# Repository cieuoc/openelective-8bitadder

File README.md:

Assignment: 8 bit full adder

+ Create a directory with your name
+ Inside it, 2 directories called Circuit, Enclosure

+ Place Kicad files and libraries inside Circuit
+ FreeCAD file FCstd and exported STL files inside Enclosure

+ Git add .
+ Git commit 
+ Git push

+ Create PR

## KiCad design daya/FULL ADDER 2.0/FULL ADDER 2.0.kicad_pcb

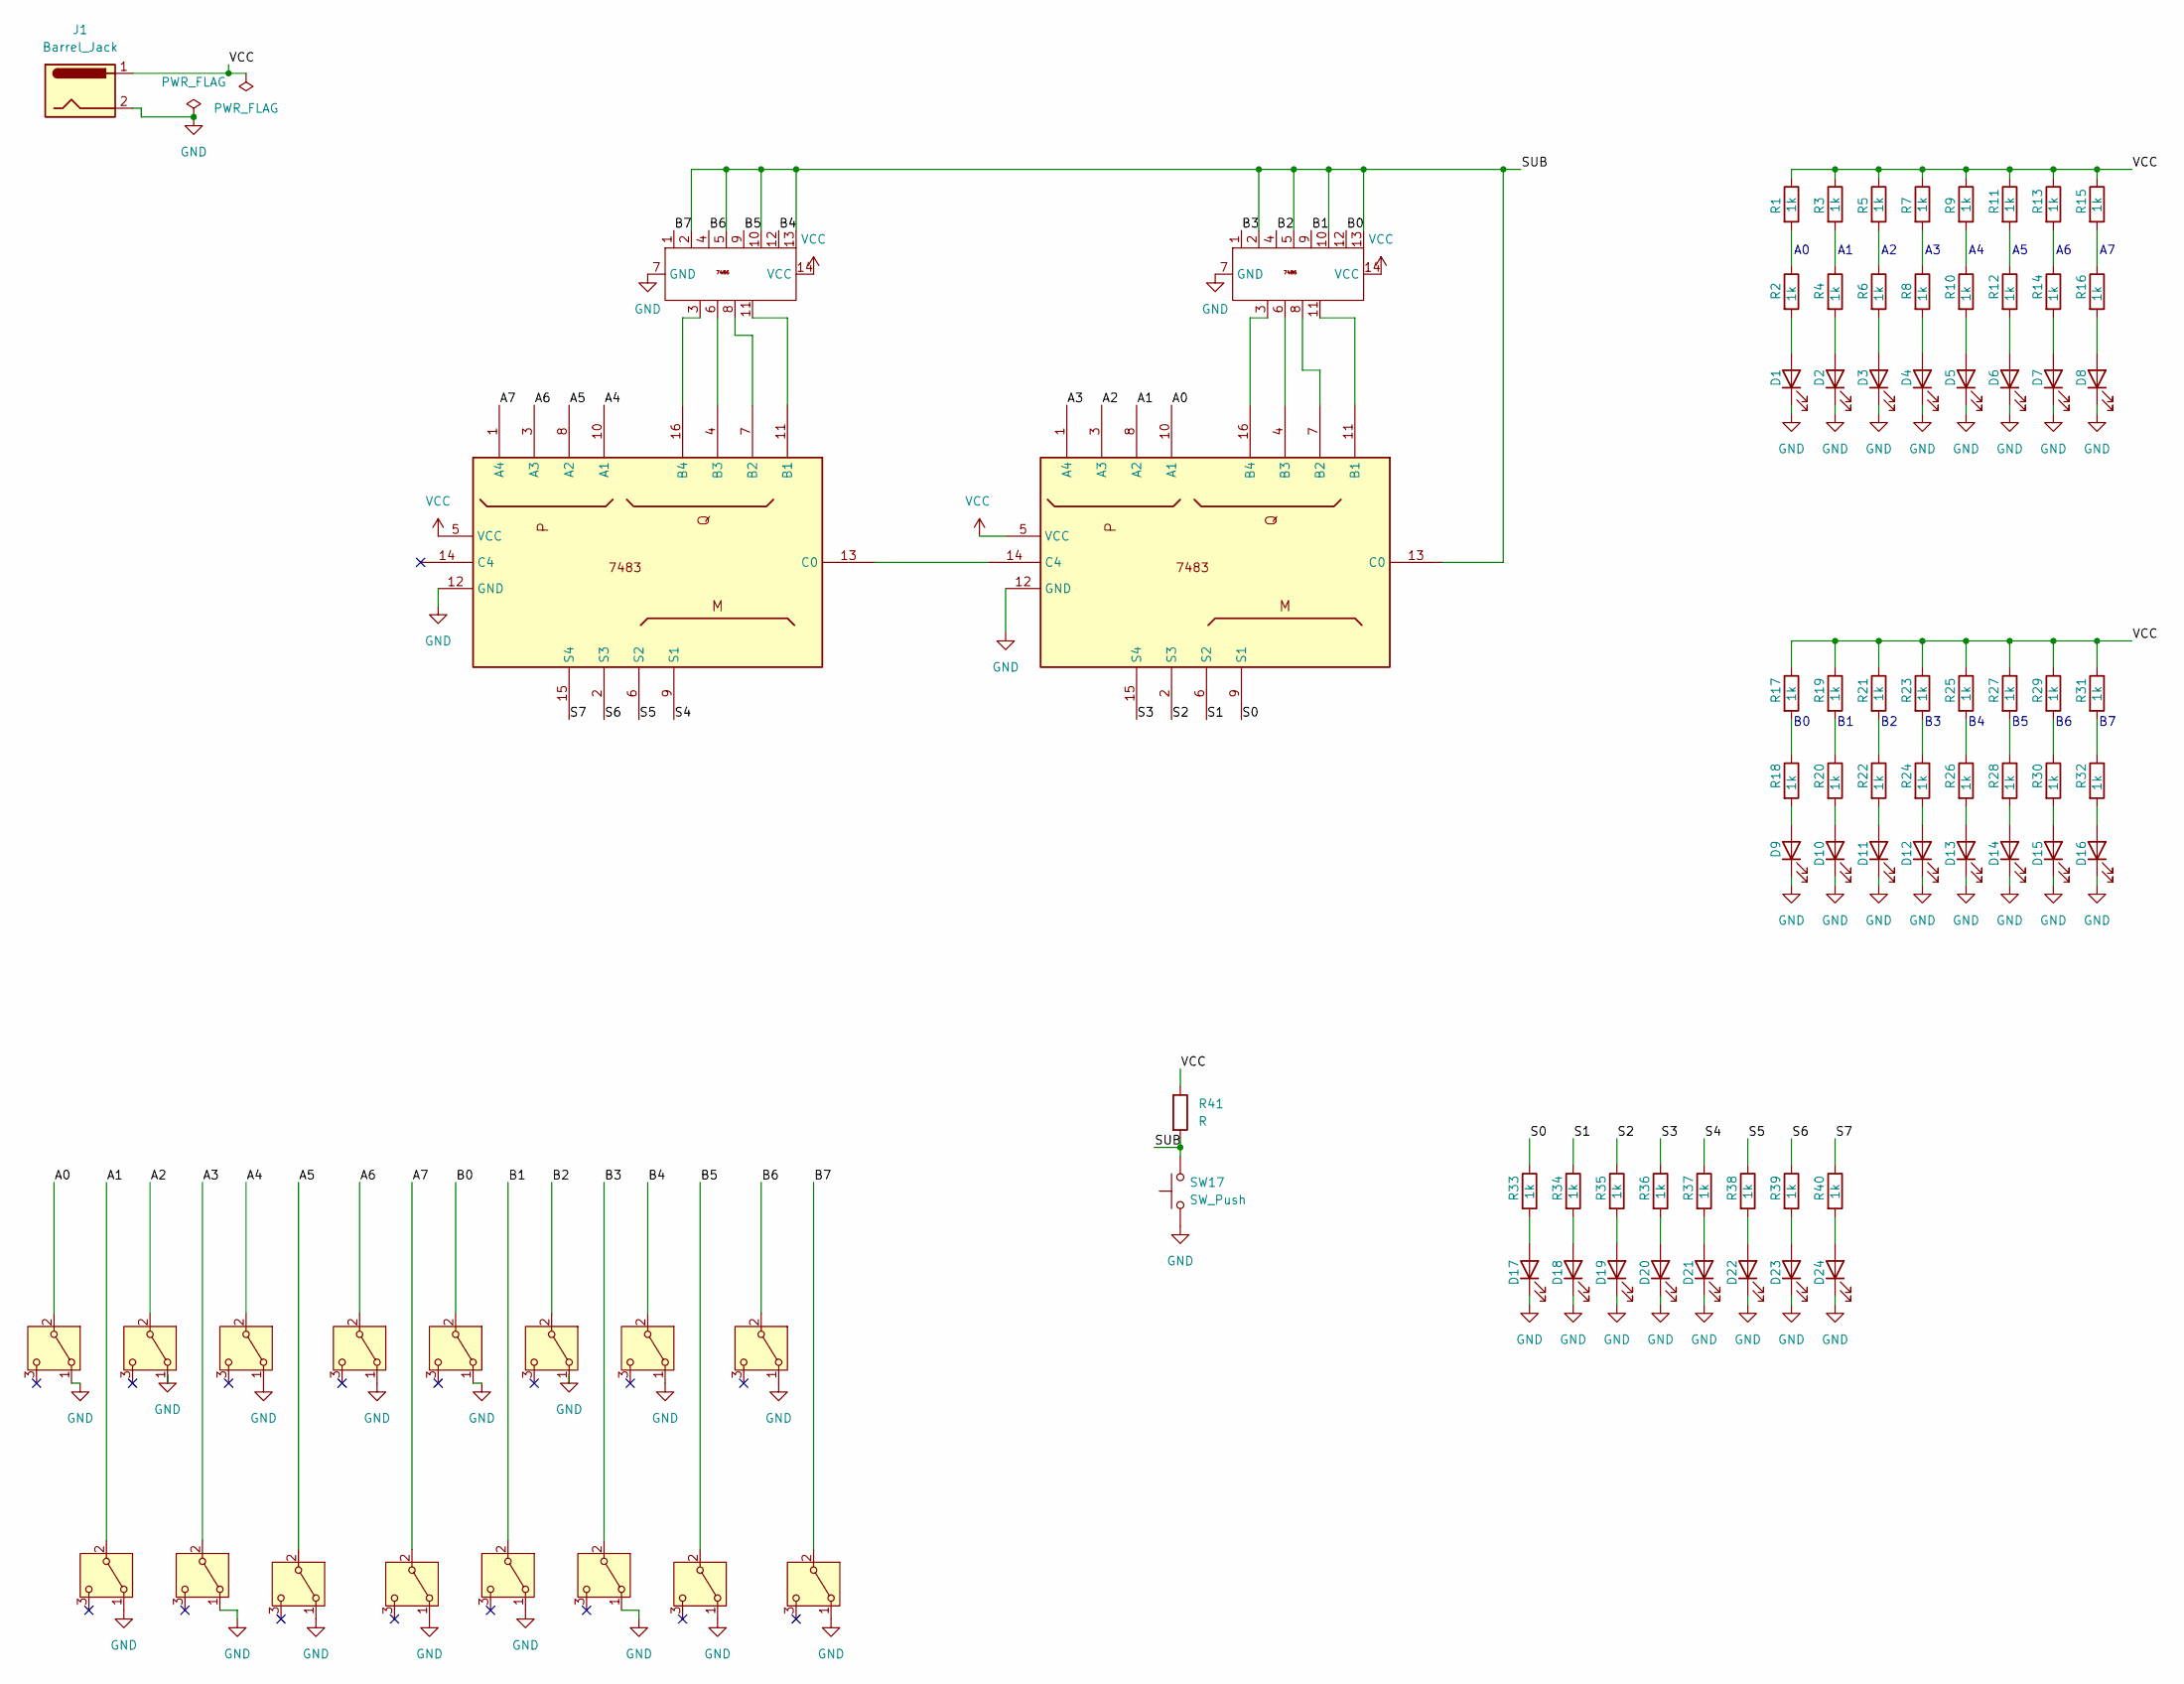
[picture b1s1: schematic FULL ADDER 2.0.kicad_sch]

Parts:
D1, D2, D3, D4, D5, D6, D7, D8, D9, D10, D11, D12, D13, D14, D15, D16, D17, D18, D19, D20, D21, D22, D23, D24: LED; LED_D3.0mm
J1: Barrel_Jack; BarrelJack_Horizontal
R1, R2, R3, R4, R5, R6, R7, R8, R9, R10, R11, R12, R13, R14, R15, R16, R17, R18, R19, R20, R21, R22, R23, R24, R25, R26, R27, R28, R29, R30, R31, R32, R33, R34, R35, R36, R37, R38, R39, R40: 1k; R_Axial_DIN0204_L3.6mm_D1.6mm_P5.08mm_Horizontal
R41: R; R_Axial_DIN0204_L3.6mm_D1.6mm_P5.08mm_Horizontal
SW1, SW2, SW3, SW4, SW5, SW6, SW7, SW8, SW9, SW10, SW11, SW12, SW13, SW14, SW15, SW16: SW_SPDT; adder switch
SW17: SW_Push; adder switch
U1, U4: DIP-16_W7.62mm
U2, U3: DIP-14_W7.62mm

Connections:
/A0: SW12.2 (B), U1.10 (A1)
/A1: SW9.2 (B), U1.8 (A2)
/A2: SW8.2 (B), U1.3 (A3)
/A3: SW6.2 (B), U1.1 (A4)
/A4: SW7.2 (B), U4.10 (A1)
/A5: SW3.2 (B), U4.8 (A2)
/A6: SW2.2 (B), U4.3 (A3)
/A7: SW4.2 (B), U4.1 (A4)
/B0: SW1.2 (B), U3.12
/B1: SW5.2 (B), U3.9
/B2: SW10.2 (B), U3.4
/B3: SW11.2 (B), U3.1
/B4: SW13.2 (B), U2.12
/B5: SW14.2 (B), U2.9
/B6: SW15.2 (B), U2.4
/B7: SW16.2 (B), U2.1
/S0: R33.1, U1.9 (S1)
/S1: R34.1, U1.6 (S2)
/S2: R35.1, U1.2 (S3)
/S3: R36.1, U1.15 (S4)
/S4: R37.1, U4.9 (S1)
/S5: R38.1, U4.6 (S2)
/S6: R39.1, U4.2 (S3)
/S7: R40.1, U4.15 (S4)
/SUB: R41.2, SW17.2, U1.13 (C0), U2.2, U2.5, U2.10, U2.13, U3.2, U3.5, U3.10, U3.13
GND: D1.1 (K), D2.1 (K), D3.1 (K), D4.1 (K), D5.1 (K), D6.1 (K), D7.1 (K), D8.1 (K), D9.1 (K), D10.1 (K), D11.1 (K), D12.1 (K), D13.1 (K), D14.1 (K), D15.1 (K), D16.1 (K), D17.1 (K), D18.1 (K), D19.1 (K), D20.1 (K), D21.1 (K), D22.1 (K), D23.1 (K), D24.1 (K), J1.2, SW1.1 (A), SW2.1 (A), SW3.1 (A), SW4.1 (A), SW5.1 (A), SW6.1 (A), SW7.1 (A), SW8.1 (A), SW9.1 (A), SW10.1 (A), SW11.1 (A), SW12.1 (A), SW13.1 (A), SW14.1 (A), SW15.1 (A), SW16.1 (A), SW17.1, U1.12 (GND), U2.7 (GND), U3.7 (GND), U4.12 (GND)
unnamed: D1.2 (A), R2.2
unnamed: D2.2 (A), R4.2
unnamed: D3.2 (A), R6.2
unnamed: D4.2 (A), R8.2
unnamed: D5.2 (A), R10.2
unnamed: D6.2 (A), R12.2
unnamed: D7.2 (A), R14.2
unnamed: D8.2 (A), R16.2
unnamed: D9.2 (A), R18.2
unnamed: D10.2 (A), R20.2
unnamed: D11.2 (A), R22.2
unnamed: D12.2 (A), R24.2
unnamed: D13.2 (A), R26.2
unnamed: D14.2 (A), R28.2
unnamed: D15.2 (A), R30.2
unnamed: D16.2 (A), R32.2
unnamed: D17.2 (A), R33.2
unnamed: D18.2 (A), R34.2
unnamed: D19.2 (A), R35.2
unnamed: D20.2 (A), R36.2
unnamed: D21.2 (A), R37.2
unnamed: D22.2 (A), R38.2
unnamed: D23.2 (A), R39.2
unnamed: D24.2 (A), R40.2
unnamed: R1.2, R2.1
unnamed: R3.2, R4.1
unnamed: R5.2, R6.1
unnamed: R7.2, R8.1
unnamed: R9.2, R10.1
unnamed: R11.2, R12.1
unnamed: R13.2, R14.1
unnamed: R15.2, R16.1
unnamed: R17.2, R18.1
unnamed: R19.2, R20.1
unnamed: R21.2, R22.1
unnamed: R23.2, R24.1
unnamed: R25.2, R26.1
unnamed: R27.2, R28.1
unnamed: R29.2, R30.1
unnamed: R31.2, R32.1
unnamed: U1.11 (B1), U3.11
unnamed: U1.7 (B2), U3.8
unnamed: U1.4 (B3), U3.6
unnamed: U1.16 (B4), U3.3
unnamed: U1.14 (C4), U4.13 (C0)
unnamed: U2.11, U4.11 (B1)
unnamed: U2.8, U4.7 (B2)
unnamed: U2.6, U4.4 (B3)
unnamed: U2.3, U4.16 (B4)
VCC: J1.1, R1.1, R3.1, R5.1, R7.1, R9.1, R11.1, R13.1, R15.1, R17.1, R19.1, R21.1, R23.1, R25.1, R27.1, R29.1, R31.1, R41.1, U1.5 (VCC), U2.14 (VCC), U3.14 (VCC), U4.5 (VCC)

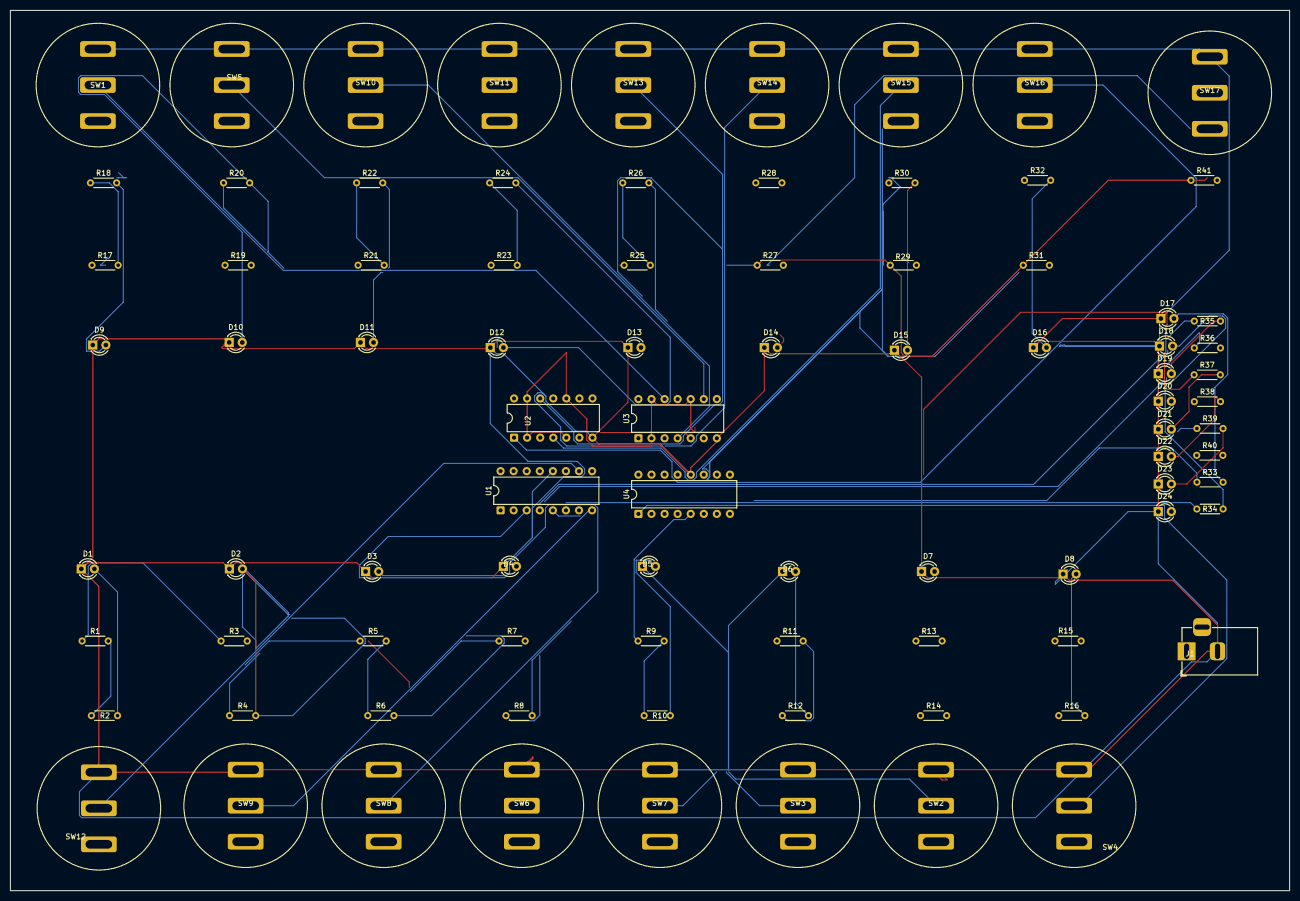
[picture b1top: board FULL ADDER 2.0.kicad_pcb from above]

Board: 2 copper layers, 248.5 x 171.0 mm, 87 parts (0 on the bottom side), 76 nets.

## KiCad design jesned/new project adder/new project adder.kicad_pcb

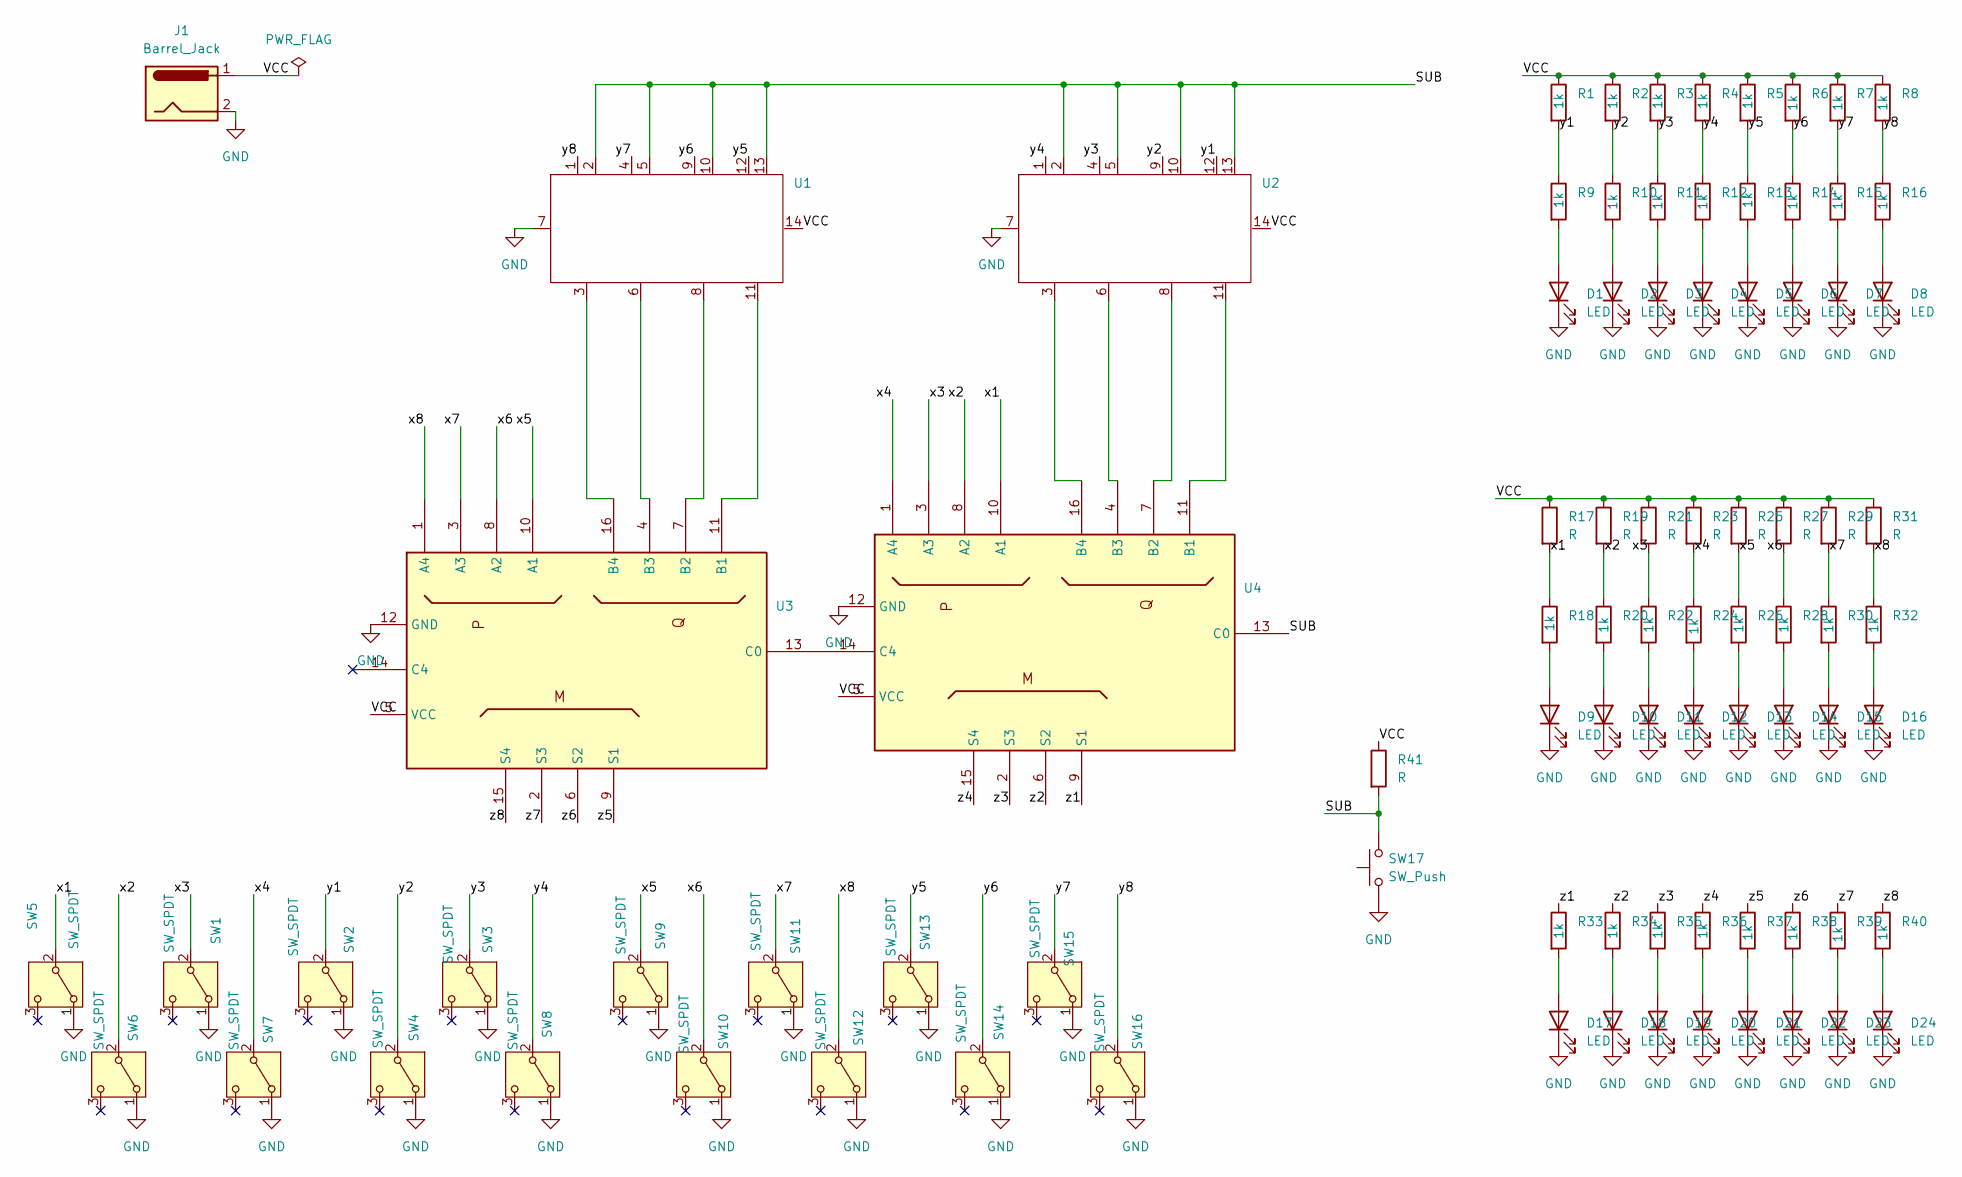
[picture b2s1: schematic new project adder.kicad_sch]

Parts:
D1, D2, D3, D4, D5, D6, D7, D8, D9, D10, D11, D12, D13, D14, D15, D16, D17, D18, D19, D20, D21, D22, D23, D24: LED; LED_D3.0mm
J1: Barrel_Jack; BarrelJack_Horizontal
R1, R2, R3, R4, R5, R6, R7, R8, R9, R10, R11, R12, R13, R14, R15, R16, R18, R20, R22, R24, R26, R28, R30, R32, R33, R34, R35, R36, R37, R38, R39, R40: 1k; R_Axial_DIN0204_L3.6mm_D1.6mm_P5.08mm_Horizontal
R17, R19, R21, R23, R25, R27, R29, R31, R41: R; R_Axial_DIN0204_L3.6mm_D1.6mm_P5.08mm_Horizontal
SW1, SW2, SW3, SW4, SW5, SW6, SW7, SW8, SW9, SW10, SW11, SW12, SW13, SW14, SW15, SW16: SW_SPDT; myswitch
SW17: SW_Push; myswitch
U1, U2: DIP-14_W7.62mm
U3, U4: DIP-16_W7.62mm

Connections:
/SUB: R41.2, SW17.2, U1.2, U1.5, U1.10, U1.13, U2.2, U2.5, U2.10, U2.13, U4.13 (C0)
/VCC: J1.1, R1.1, R2.1, R3.1, R4.1, R5.1, R6.1, R7.1, R8.1, R17.1, R19.1, R21.1, R23.1, R25.1, R27.1, R29.1, R31.1, R41.1, U1.14, U2.14, U3.5 (VCC), U4.5 (VCC)
/x1: R17.2, R18.1, SW5.2 (B), U4.10 (A1)
/x2: R19.2, R20.1, SW6.2 (B), U4.8 (A2)
/x3: R21.2, R22.1, SW1.2 (B), U4.3 (A3)
/x4: R23.2, R24.1, SW7.2 (B), U4.1 (A4)
/x5: R25.2, R26.1, SW9.2 (B), U3.10 (A1)
/x6: R27.2, R28.1, SW10.2 (B), U3.8 (A2)
/x7: R29.2, R30.1, SW11.2 (B), U3.3 (A3)
/x8: R31.2, R32.1, SW12.2 (B), U3.1 (A4)
/y1: R1.2, R9.1, SW2.2 (B), U2.12
/y2: R2.2, R10.1, SW4.2 (B), U2.9
/y3: R3.2, R11.1, SW3.2 (B), U2.4
/y4: R4.2, R12.1, SW8.2 (B), U2.1
/y5: R5.2, R13.1, SW13.2 (B), U1.12
/y6: R6.2, R14.1, SW14.2 (B), U1.9
/y7: R7.2, R15.1, SW15.2 (B), U1.4
/y8: R8.2, R16.1, SW16.2 (B), U1.1
/z1: R33.1, U4.9 (S1)
/z2: R34.1, U4.6 (S2)
/z3: R35.1, U4.2 (S3)
/z4: R36.1, U4.15 (S4)
/z5: R37.1, U3.9 (S1)
/z6: R38.1, U3.6 (S2)
/z7: R39.1, U3.2 (S3)
/z8: R40.1, U3.15 (S4)
GND: D1.1 (K), D2.1 (K), D3.1 (K), D4.1 (K), D5.1 (K), D6.1 (K), D7.1 (K), D8.1 (K), D9.1 (K), D10.1 (K), D11.1 (K), D12.1 (K), D13.1 (K), D14.1 (K), D15.1 (K), D16.1 (K), D17.1 (K), D18.1 (K), D19.1 (K), D20.1 (K), D21.1 (K), D22.1 (K), D23.1 (K), D24.1 (K), J1.2, SW1.1 (A), SW2.1 (A), SW3.1 (A), SW4.1 (A), SW5.1 (A), SW6.1 (A), SW7.1 (A), SW8.1 (A), SW9.1 (A), SW10.1 (A), SW11.1 (A), SW12.1 (A), SW13.1 (A), SW14.1 (A), SW15.1 (A), SW16.1 (A), SW17.1, U1.7, U2.7, U3.12 (GND), U4.12 (GND)
unnamed: D1.2 (A), R9.2
unnamed: D2.2 (A), R10.2
unnamed: D3.2 (A), R11.2
unnamed: D4.2 (A), R12.2
unnamed: D5.2 (A), R13.2
unnamed: D6.2 (A), R14.2
unnamed: D7.2 (A), R15.2
unnamed: D8.2 (A), R16.2
unnamed: D9.2 (A), R18.2
unnamed: D10.2 (A), R20.2
unnamed: D11.2 (A), R22.2
unnamed: D12.2 (A), R24.2
unnamed: D13.2 (A), R26.2
unnamed: D14.2 (A), R28.2
unnamed: D15.2 (A), R30.2
unnamed: D16.2 (A), R32.2
unnamed: D17.2 (A), R33.2
unnamed: D18.2 (A), R34.2
unnamed: D19.2 (A), R35.2
unnamed: D20.2 (A), R36.2
unnamed: D21.2 (A), R37.2
unnamed: D22.2 (A), R38.2
unnamed: D23.2 (A), R39.2
unnamed: D24.2 (A), R40.2
unnamed: U1.11, U3.11 (B1)
unnamed: U1.8, U3.7 (B2)
unnamed: U1.6, U3.4 (B3)
unnamed: U1.3, U3.16 (B4)
unnamed: U3.13 (C0), U4.14 (C4)
unnamed: U2.11, U4.11 (B1)
unnamed: U2.8, U4.7 (B2)
unnamed: U2.6, U4.4 (B3)
unnamed: U2.3, U4.16 (B4)

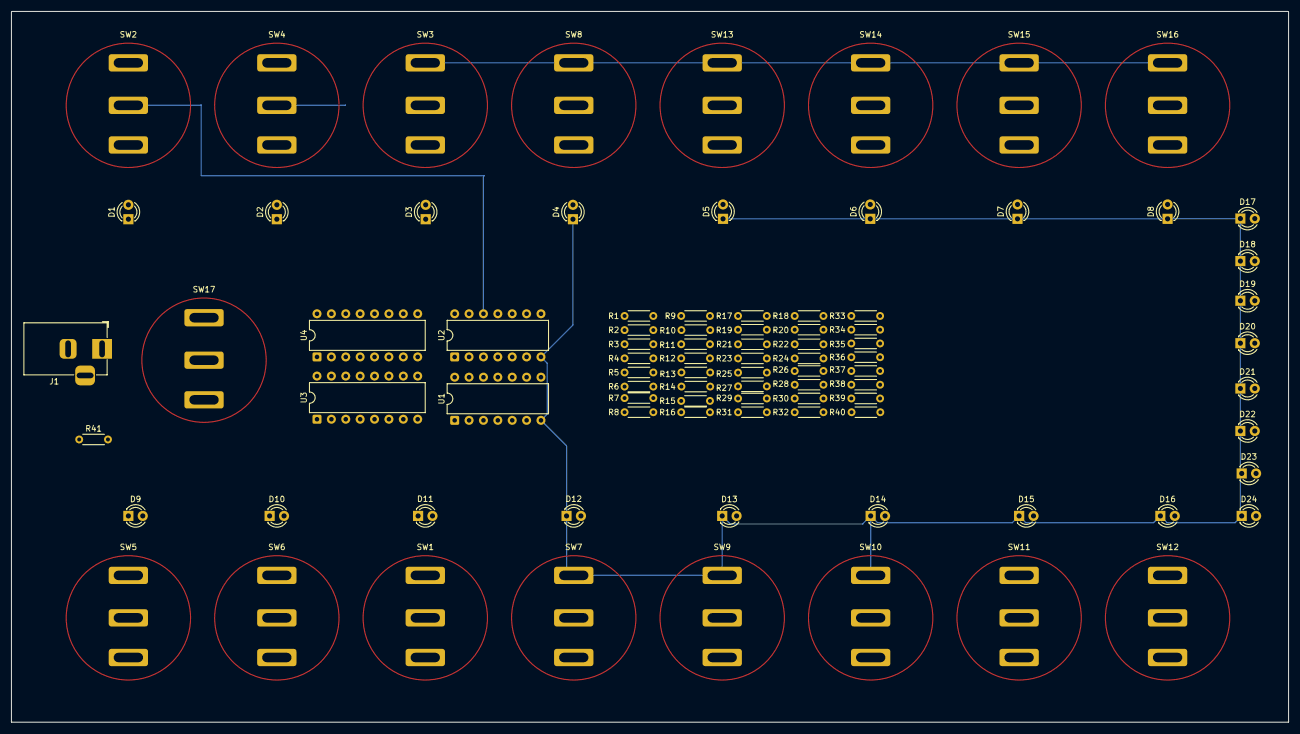
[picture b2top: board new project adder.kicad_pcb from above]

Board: 2 copper layers, 225.5 x 125.5 mm, 87 parts (0 on the bottom side), 60 nets.

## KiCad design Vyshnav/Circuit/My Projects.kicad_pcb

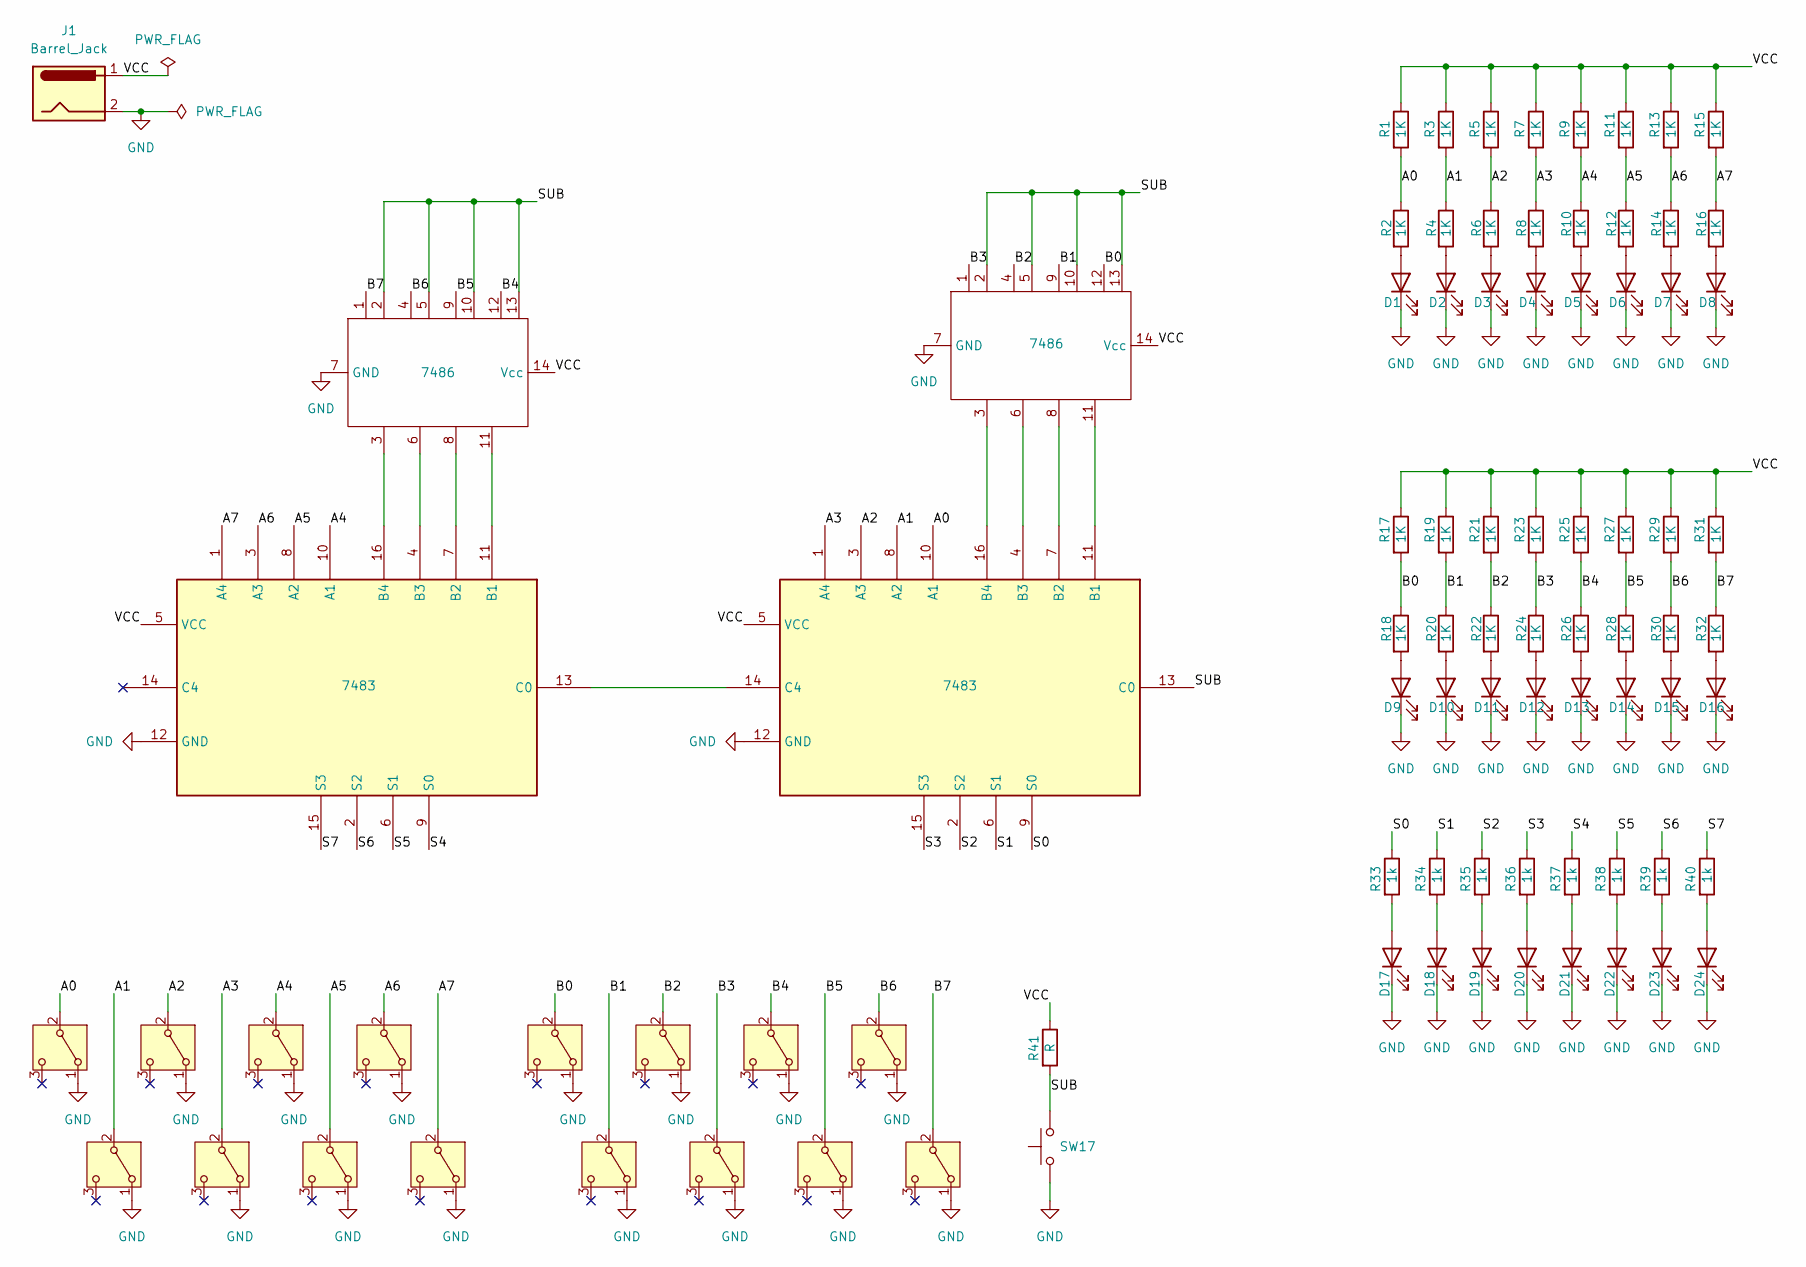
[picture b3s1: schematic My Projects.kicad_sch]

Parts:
D1, D2, D3, D4, D5, D6, D7, D8, D9, D10, D11, D12, D13, D14, D15, D16, D17, D18, D19, D20, D21, D22, D23, D24: LED; LED_D3.0mm
IC1, IC2: 7483; SMDIP-16_W7.62mm
IC3, IC4: 7486; DIP-14_W7.62mm
J1: Barrel_Jack; BarrelJack_Horizontal
R1, R2, R3, R4, R5, R6, R7, R8, R9, R10, R11, R12, R13, R14, R15, R16, R17, R18, R19, R20, R21, R22, R23, R24, R25, R26, R27, R28, R29, R30, R31, R32: 1K; R_Axial_DIN0204_L3.6mm_D1.6mm_P5.08mm_Horizontal
R33, R34, R35, R36, R37, R38, R39, R40: 1k; R_Axial_DIN0204_L3.6mm_D1.6mm_P5.08mm_Horizontal
R41: R; R_Axial_DIN0204_L3.6mm_D1.6mm_P5.08mm_Horizontal
SW1, SW2, SW3, SW4, SW5, SW6, SW7, SW8, SW9, SW10, SW11, SW12, SW13, SW14, SW15, SW16: SW_SPDT; SWITCH
SW17: SW_Push; SW_PUSH_6mm

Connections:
/A0: IC2.10 (A1), R1.2, R2.1, SW1.2 (B)
/A1: IC2.8 (A2), R3.2, R4.1, SW5.2 (B)
/A2: IC2.3 (A3), R5.2, R6.1, SW2.2 (B)
/A3: IC2.1 (A4), R7.2, R8.1, SW3.2 (B)
/A4: IC1.10 (A1), R9.2, R10.1, SW4.2 (B)
/A5: IC1.8 (A2), R11.2, R12.1, SW6.2 (B)
/A6: IC1.3 (A3), R13.2, R14.1, SW7.2 (B)
/A7: IC1.1 (A4), R15.2, R16.1, SW8.2 (B)
/B0: IC4.12, R17.2, R18.1, SW9.2 (B)
/B1: IC4.9, R19.2, R20.1, SW10.2 (B)
/B2: IC4.4, R21.2, R22.1, SW11.2 (B)
/B3: IC4.1, R23.2, R24.1, SW12.2 (B)
/B4: IC3.12, R25.2, R26.1, SW13.2 (B)
/B5: IC3.9, R27.2, R28.1, SW14.2 (B)
/B6: IC3.4, R29.2, R30.1, SW15.2 (B)
/B7: IC3.1, R31.2, R32.1, SW16.2 (B)
/S0: IC2.9 (S0), R33.1
/S1: IC2.6 (S1), R34.1
/S2: IC2.2 (S2), R35.1
/S3: IC2.15 (S3), R36.1
/S4: IC1.9 (S0), R37.1
/S5: IC1.6 (S1), R38.1
/S6: IC1.2 (S2), R39.1
/S7: IC1.15 (S3), R40.1
/SUB: IC2.13 (C0), IC3.2, IC3.5, IC3.10, IC3.13, IC4.2, IC4.5, IC4.10, IC4.13, R41.2, SW17.2
/VCC: IC1.5 (VCC), IC2.5 (VCC), IC3.14 (Vcc), IC4.14 (Vcc), J1.1, R1.1, R3.1, R5.1, R7.1, R9.1, R11.1, R13.1, R15.1, R17.1, R19.1, R21.1, R23.1, R25.1, R27.1, R29.1, R31.1, R41.1
GND: D1.1 (K), D2.1 (K), D3.1 (K), D4.1 (K), D5.1 (K), D6.1 (K), D7.1 (K), D8.1 (K), D9.1 (K), D10.1 (K), D11.1 (K), D12.1 (K), D13.1 (K), D14.1 (K), D15.1 (K), D16.1 (K), D17.1 (K), D18.1 (K), D19.1 (K), D20.1 (K), D21.1 (K), D22.1 (K), D23.1 (K), D24.1 (K), IC1.12 (GND), IC2.12 (GND), IC3.7 (GND), IC4.7 (GND), J1.2, SW1.1 (A), SW2.1 (A), SW3.1 (A), SW4.1 (A), SW5.1 (A), SW6.1 (A), SW7.1 (A), SW8.1 (A), SW9.1 (A), SW10.1 (A), SW11.1 (A), SW12.1 (A), SW13.1 (A), SW14.1 (A), SW15.1 (A), SW16.1 (A), SW17.1
unnamed: D1.2 (A), R2.2
unnamed: D2.2 (A), R4.2
unnamed: D3.2 (A), R6.2
unnamed: D4.2 (A), R8.2
unnamed: D5.2 (A), R10.2
unnamed: D6.2 (A), R12.2
unnamed: D7.2 (A), R14.2
unnamed: D8.2 (A), R16.2
unnamed: D9.2 (A), R18.2
unnamed: D10.2 (A), R20.2
unnamed: D11.2 (A), R22.2
unnamed: D12.2 (A), R24.2
unnamed: D13.2 (A), R26.2
unnamed: D14.2 (A), R28.2
unnamed: D15.2 (A), R30.2
unnamed: D16.2 (A), R32.2
unnamed: D17.2 (A), R33.2
unnamed: D18.2 (A), R34.2
unnamed: D19.2 (A), R35.2
unnamed: D20.2 (A), R36.2
unnamed: D21.2 (A), R37.2
unnamed: D22.2 (A), R38.2
unnamed: D23.2 (A), R39.2
unnamed: D24.2 (A), R40.2
unnamed: IC1.11 (B1), IC3.11
unnamed: IC1.7 (B2), IC3.8
unnamed: IC1.4 (B3), IC3.6
unnamed: IC1.16 (B4), IC3.3
unnamed: IC1.13 (C0), IC2.14 (C4)
unnamed: IC2.11 (B1), IC4.11
unnamed: IC2.7 (B2), IC4.8
unnamed: IC2.4 (B3), IC4.6
unnamed: IC2.16 (B4), IC4.3

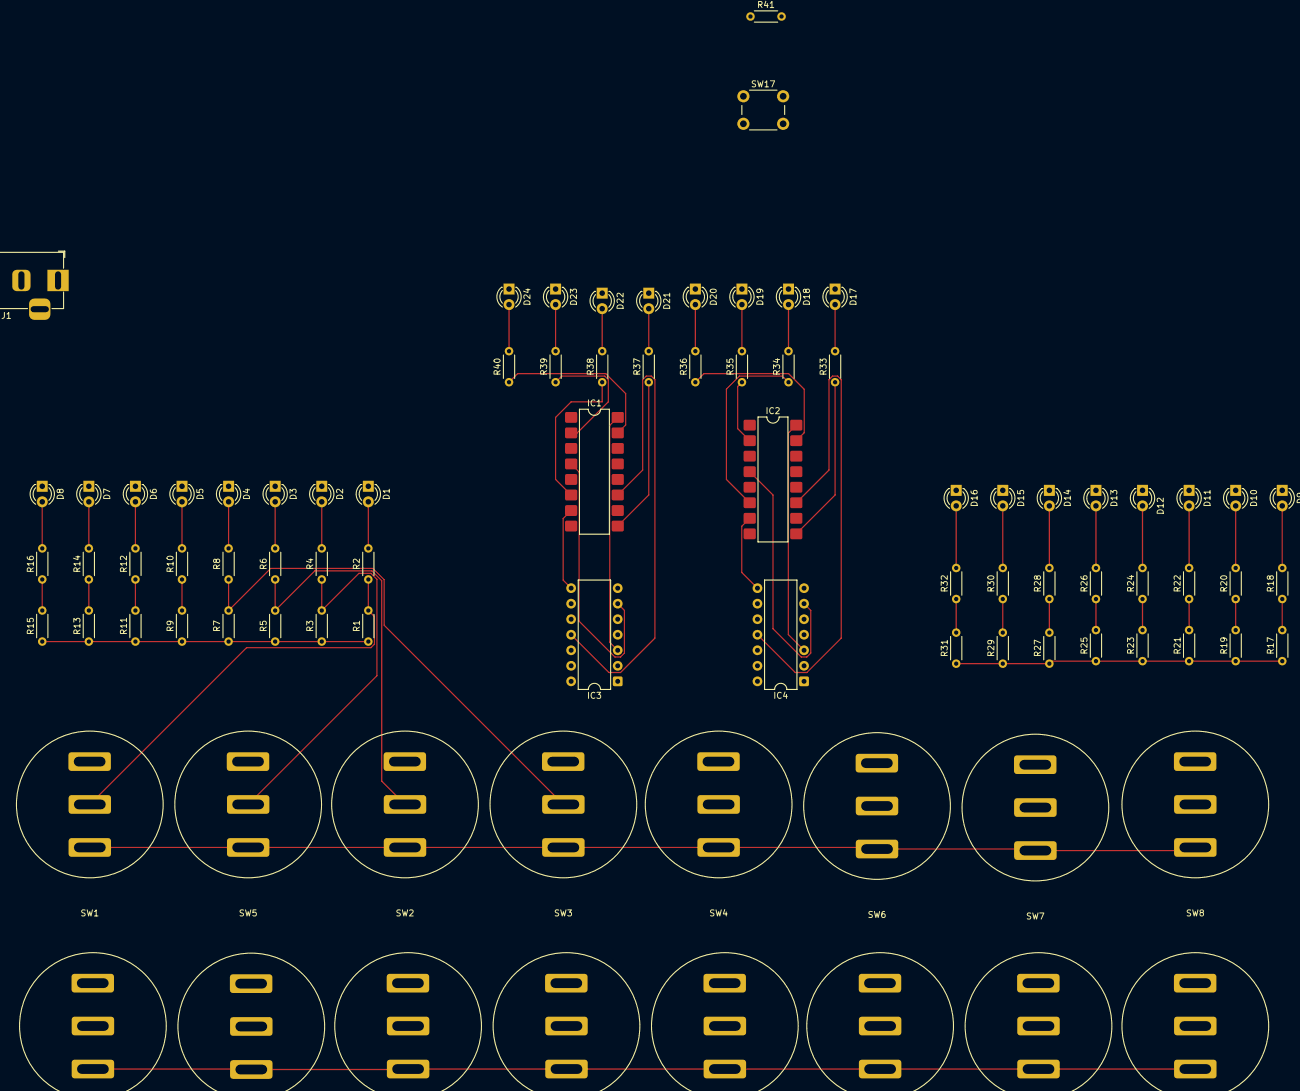
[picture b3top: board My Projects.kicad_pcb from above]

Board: 2 copper layers, 87 parts (0 on the bottom side), 60 nets.

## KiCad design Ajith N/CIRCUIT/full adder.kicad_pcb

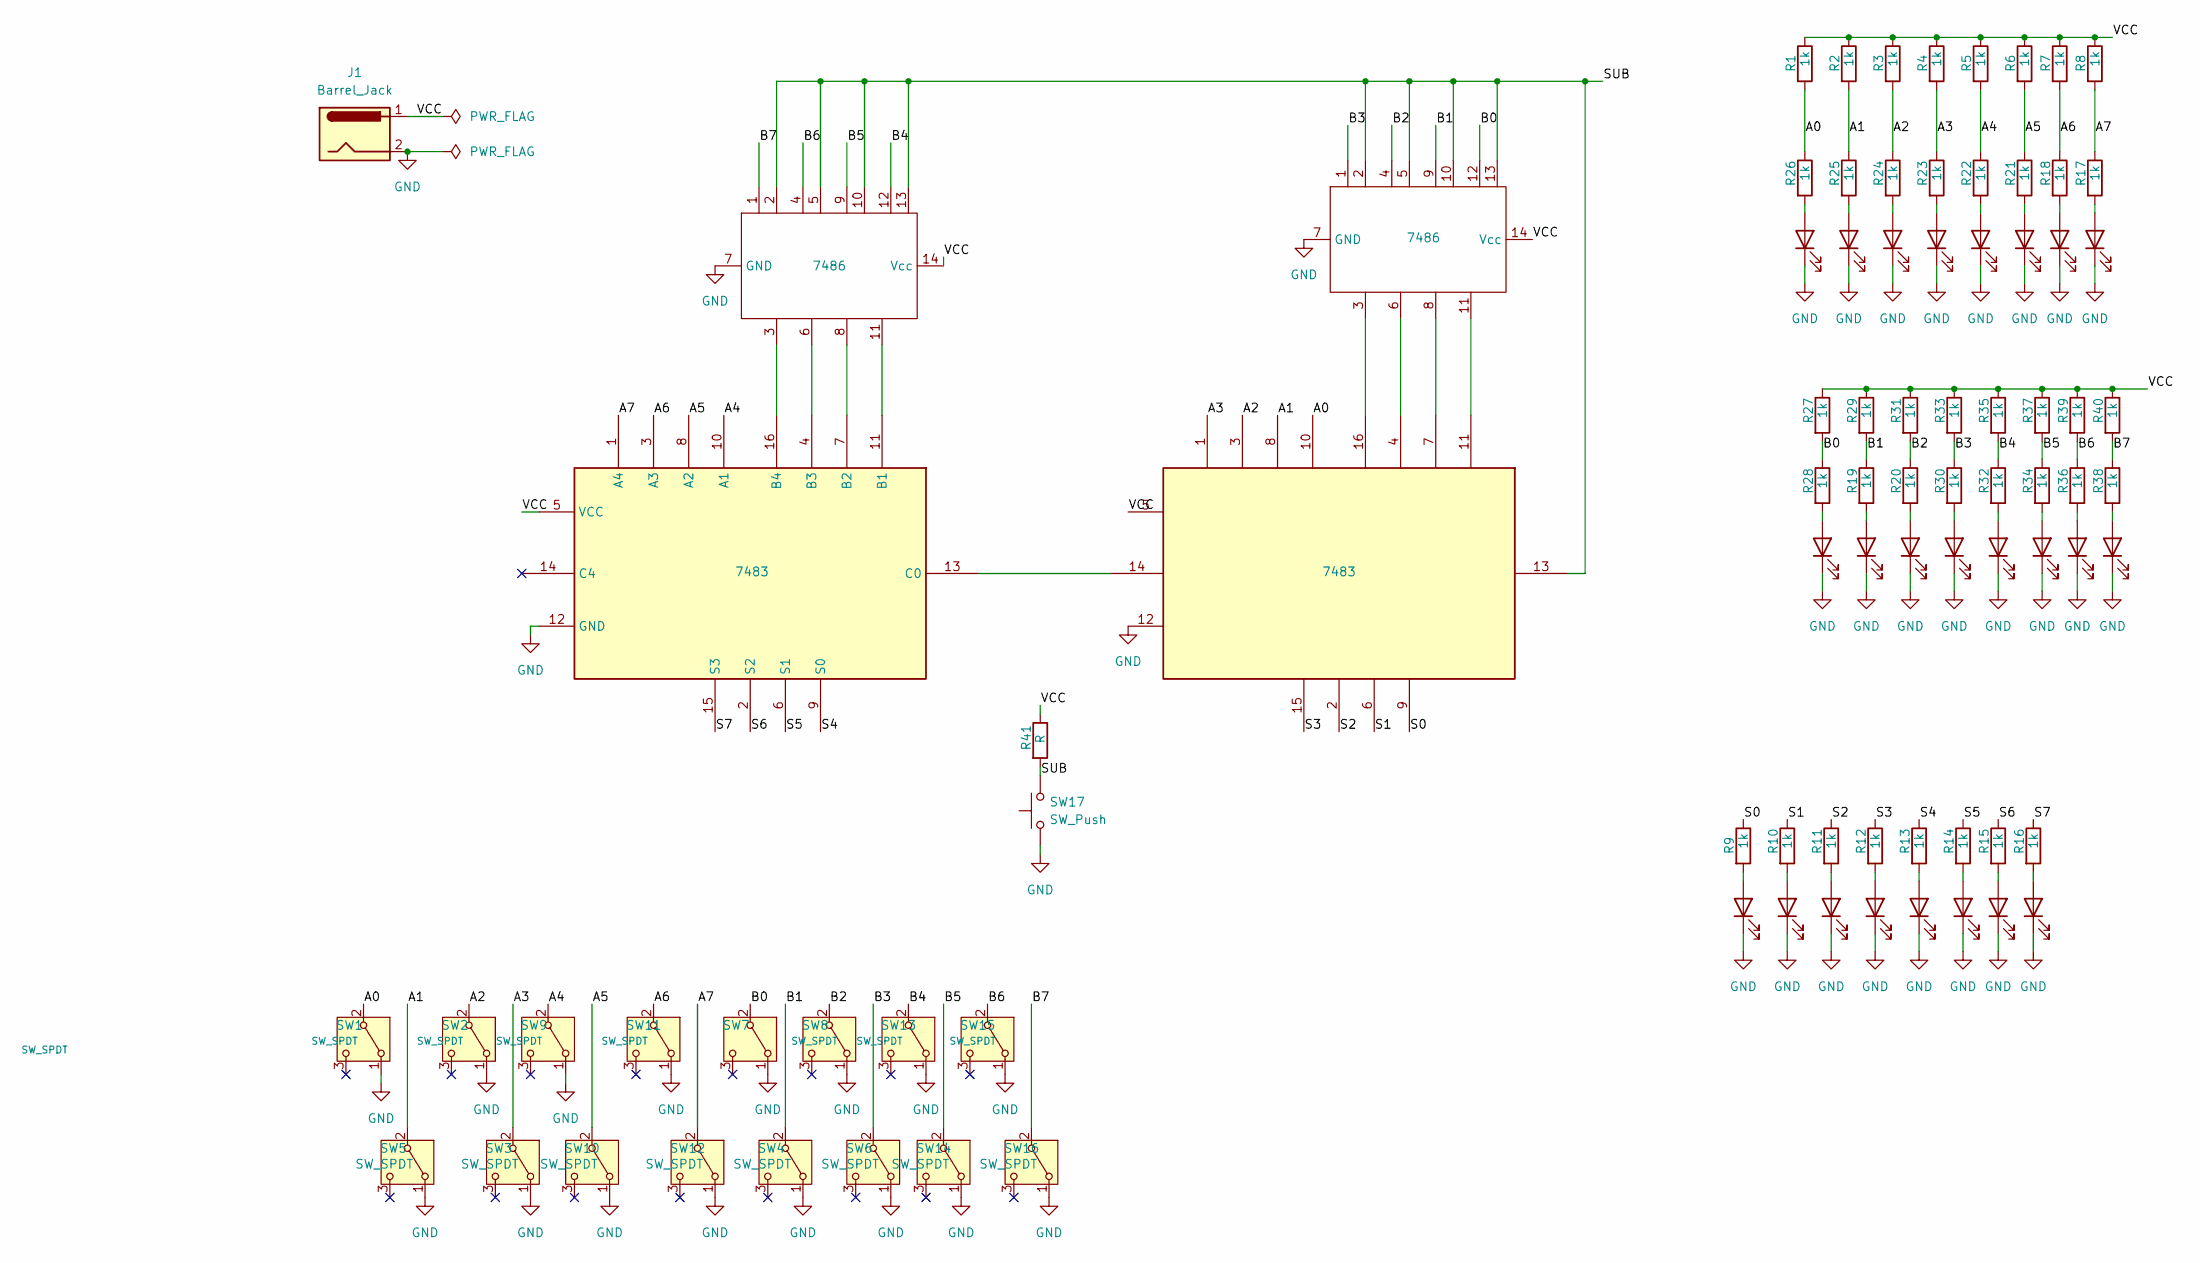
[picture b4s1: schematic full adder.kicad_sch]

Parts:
D1, D2, D3, D4, D5, D6, D7, D8, D9, D10, D11, D12, D13, D14, D15, D16, D18, D19, D20, D21, D22, D23, D24, D25: LED; LED_D3.0mm
IC1, IC2: 7483; DIP-16_W7.62mm
IC3, IC4: 7486; DIP-14_W7.62mm
J1: Barrel_Jack; BarrelJack_GCT_DCJ200-10-A_Horizontal
R1, R2, R3, R4, R5, R6, R7, R8, R9, R10, R11, R12, R13, R14, R15, R16, R17, R18, R19, R20, R21, R22, R23, R24, R25, R26, R27, R28, R29, R30, R31, R32, R33, R34, R35, R36, R37, R38, R39, R40: 1k; R_Axial_DIN0204_L3.6mm_D1.6mm_P5.08mm_Horizontal
R41: R; R_Axial_DIN0204_L3.6mm_D1.6mm_P5.08mm_Horizontal
SW1, SW2, SW3, SW4, SW5, SW6, SW7, SW8, SW9, SW10, SW11, SW12, SW13, SW14, SW15, SW16: SW_SPDT; LED SWITCH3pin
SW17: SW_Push; SW_PUSH_6mm

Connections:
/A0: IC2.10 (A1), R1.2, R26.1, SW1.2 (B)
/A1: IC2.8 (A2), R2.2, R25.1, SW5.2 (B)
/A2: IC2.3 (A3), R3.2, R24.1, SW2.2 (B)
/A3: IC2.1 (A4), R4.2, R23.1, SW3.2 (B)
/A4: IC1.10 (A1), R5.2, R22.1, SW9.2 (B)
/A5: IC1.8 (A2), R6.2, R21.1, SW10.2 (B)
/A6: IC1.3 (A3), R7.2, R18.1, SW11.2 (B)
/A7: IC1.1 (A4), R8.2, R17.1, SW12.2 (B)
/B0: IC4.12, R27.2, R28.1, SW7.2 (B)
/B1: IC4.9, R19.1, R29.2, SW4.2 (B)
/B2: IC4.4, R20.1, R31.2, SW8.2 (B)
/B3: IC4.1, R30.1, R33.2, SW6.2 (B)
/B4: IC3.12, R32.1, R35.2, SW13.2 (B)
/B5: IC3.9, R34.1, R37.2, SW14.2 (B)
/B6: IC3.4, R36.1, R39.2, SW15.2 (B)
/B7: IC3.1, R38.1, R40.2, SW16.2 (B)
/S0: IC2.9 (S0), R9.1
/S1: IC2.6 (S1), R10.1
/S2: IC2.2 (S2), R11.1
/S3: IC2.15 (S3), R12.1
/S4: IC1.9 (S0), R13.1
/S5: IC1.6 (S1), R14.1
/S6: IC1.2 (S2), R15.1
/S7: IC1.15 (S3), R16.1
/SUB: IC2.13 (C0), IC3.2, IC3.5, IC3.10, IC3.13, IC4.2, IC4.5, IC4.10, IC4.13, R41.2, SW17.2
/VCC: IC1.5 (VCC), IC2.5 (VCC), IC3.14 (Vcc), IC4.14 (Vcc), J1.1, R1.1, R2.1, R3.1, R4.1, R5.1, R6.1, R7.1, R8.1, R27.1, R29.1, R31.1, R33.1, R35.1, R37.1, R39.1, R40.1, R41.1
GND: D1.1 (K), D2.1 (K), D3.1 (K), D4.1 (K), D5.1 (K), D6.1 (K), D7.1 (K), D8.1 (K), D9.1 (K), D10.1 (K), D11.1 (K), D12.1 (K), D13.1 (K), D14.1 (K), D15.1 (K), D16.1 (K), D18.1 (K), D19.1 (K), D20.1 (K), D21.1 (K), D22.1 (K), D23.1 (K), D24.1 (K), D25.1 (K), IC1.12 (GND), IC2.12 (GND), IC3.7 (GND), IC4.7 (GND), J1.2, SW1.1 (A), SW2.1 (A), SW3.1 (A), SW4.1 (A), SW5.1 (A), SW6.1 (A), SW7.1 (A), SW8.1 (A), SW9.1 (A), SW10.1 (A), SW11.1 (A), SW12.1 (A), SW13.1 (A), SW14.1 (A), SW15.1 (A), SW16.1 (A), SW17.1
unnamed: D1.2 (A), R26.2
unnamed: D2.2 (A), R25.2
unnamed: D3.2 (A), R24.2
unnamed: D4.2 (A), R23.2
unnamed: D5.2 (A), R22.2
unnamed: D6.2 (A), R21.2
unnamed: D7.2 (A), R18.2
unnamed: D8.2 (A), R17.2
unnamed: D9.2 (A), R9.2
unnamed: D10.2 (A), R10.2
unnamed: D11.2 (A), R11.2
unnamed: D12.2 (A), R12.2
unnamed: D13.2 (A), R13.2
unnamed: D14.2 (A), R14.2
unnamed: D15.2 (A), R15.2
unnamed: D16.2 (A), R16.2
unnamed: D18.2 (A), R28.2
unnamed: D19.2 (A), R19.2
unnamed: D20.2 (A), R20.2
unnamed: D21.2 (A), R30.2
unnamed: D22.2 (A), R32.2
unnamed: D23.2 (A), R34.2
unnamed: D24.2 (A), R36.2
unnamed: D25.2 (A), R38.2
unnamed: IC1.11 (B1), IC3.11
unnamed: IC1.7 (B2), IC3.8
unnamed: IC1.4 (B3), IC3.6
unnamed: IC1.16 (B4), IC3.3
unnamed: IC1.13 (C0), IC2.14 (C4)
unnamed: IC2.11 (B1), IC4.11
unnamed: IC2.7 (B2), IC4.8
unnamed: IC2.4 (B3), IC4.6
unnamed: IC2.16 (B4), IC4.3
